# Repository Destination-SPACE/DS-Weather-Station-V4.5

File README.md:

<div align="center">
    
    <h1>Destination Weather Station v4.5.2</h1>
    <p>An Open Source Remote Sensing Platform for National Taiwan Normal University 🇹🇼</p>
</div>

## 🌟 About the Project
Destination Weather Station is the the latest version of remote sensing tools developed to teach students across Taiwan about climate science and remote sensing in partnership with National Taiwan Normal University.
## ⚙️ Hardware
All hardware files can be found [here](hardware/destinationWeatherStation_v4-5/)
## 💻 Software
All program files can be found [here](software)
## 🗂️ Documentation
Documentation for the weather station can be found [here](https://destination-space.gitlab.io/ds-weather-station-v4.5/)
## Licenses
Each of the above sections are individually licensed. Terms and conditions apply within their respective folders.

**Documentation - [Apache License 2.0](docs/LICENSE)** <br>
**Hardware - [CERN-OHL-P](hardware/destinationWeatherStation_v4-5//LICENSE)** <br>
**Software - [The MIT License](software/LICENSE)**

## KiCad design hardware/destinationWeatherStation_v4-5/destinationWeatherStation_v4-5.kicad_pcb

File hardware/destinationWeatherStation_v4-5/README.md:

# Destination Weather Station v4.5 Hardware
KiCad files for Destination Weather Station v4.5

## KiCanvas
View schematic and PCB files with [KiCanvas](https://kicanvas.org/?github=https%3A%2F%2Fgithub.com%2FDestination-SPACE%2FDS-Weather-Station-V4_5%2Ftree%2Fmain%2Fhardware%2FdestinationWeatherStation_v4-5)

## Directory
### [🧾 Bill of Materials](bom/bom.md)
### [📄 Datasheets](datasheets)
### [📐 Gerbers](gerber)
### [📰 Schematics](pdf)

Licensed under [CERN-OHL-P](LICENSE)

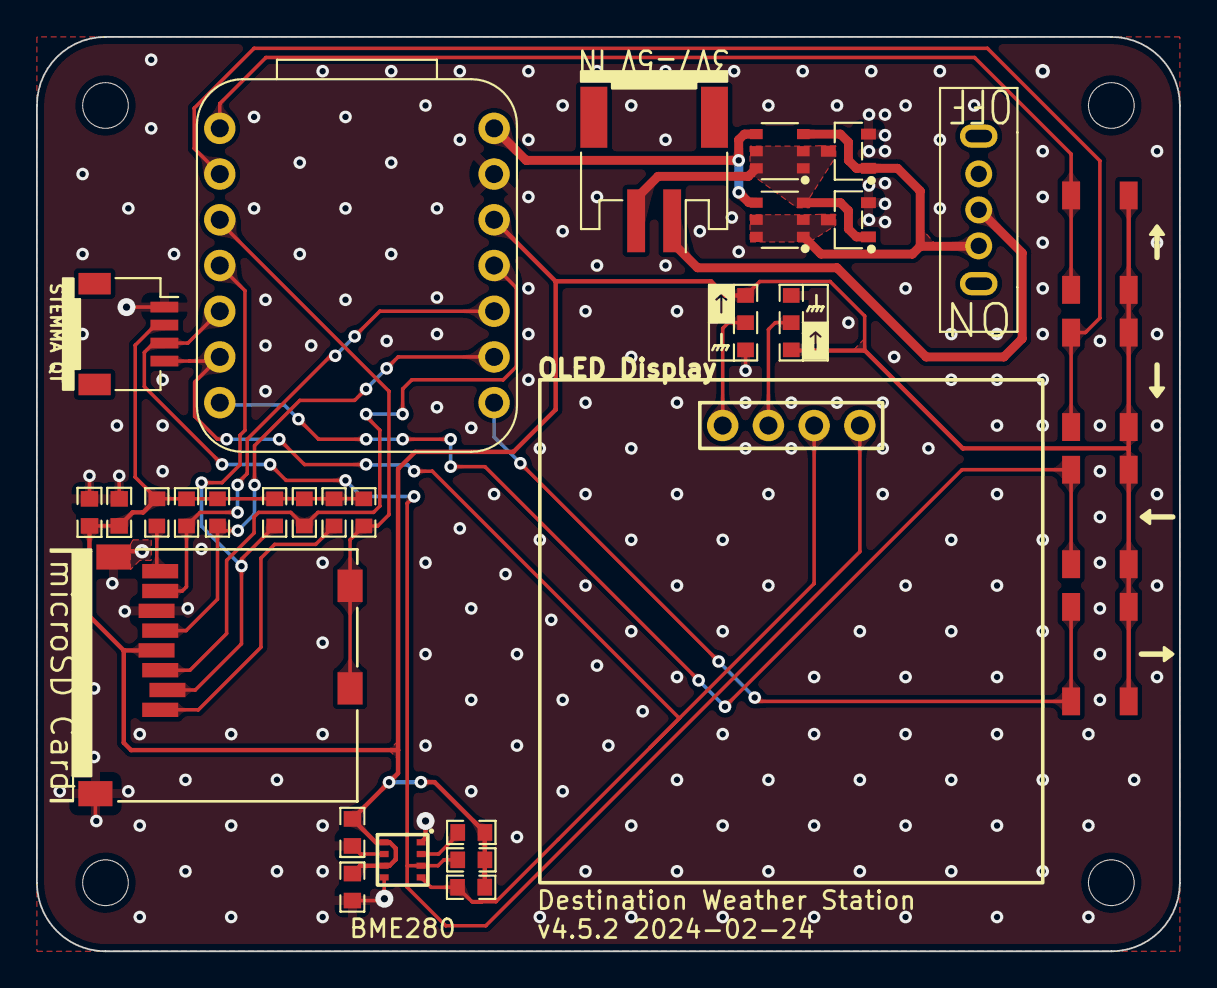
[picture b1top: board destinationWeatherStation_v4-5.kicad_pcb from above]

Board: 2 copper layers, 63.5 x 50.8 mm, 35 parts (0 on the bottom side), 22 nets.

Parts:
C1: 10uF; CAPC160X80X88L35N
C2, C3, C4: 100nF; CAPC160X80X88L35N
H1, H2, H3, H4: M2.5; M2.54_NPTH
J1: S2B-PH-SM4; JST-PH-S2B-SM4-TB
J2: MEM2061
J3: STEMMA_QT; JST_SH_SM04B-SRSS-TB
Q1, Q2: IRLML6244TRPBF
Q3, Q4: DMP2035UVTQ-7; SOT23-6P95_280X100L40X37N
R1, R2, R3, R4, R5, R6, R7, R8, R9, R10: 10K; RESC160X80X55L30N
R11, R12: 0R; ResistorJumper-3
SW1: SS-12F44-G5; SS-12D07-VG_GA_PA
SW2, SW3, SW4, SW5: PTS647SM38SMTR2LFS; SW_4.5x4.5
U1: XIAO RP2040; QtPy
U2: BME280
U3: HS96L03W2C03

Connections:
+3V3: C1.1, C2.1, C3.1, C4.1, J2.4 (VDD), J3.2, R1.1, R2.1, R3.1, R4.1, R5.1, R6.1, R7.1, R8.1, R9.1, R10.1, R11.1 (A), R12.3 (B), SW2.1, SW2.2, SW3.1, SW3.2, SW4.1, SW4.2, SW5.1, SW5.2, U1.12 (3V3), U2.6 (VDDIO), U2.8 (VDD)
/BME_CS: R8.2, U2.2 (CSB)
/CD: J2.9 (DET), R1.2, U1.3 (D2)
/CS_SD: J2.2 (DAT3/CD), R6.2, U1.4 (D3)
/DAT1: J2.8 (DAT1), R2.2
/DAT2: J2.1 (DAT2), R7.2
/MISO: J2.7 (DAT0), R3.2, U1.10 (D9)
/MOSI: J2.3 (CMD), R5.2, U1.11 (D10)
/OLED1: R11.2 (C), U3.1 (GND)
/OLED2: R12.2 (C), U3.2 (VCC)
/SCK: J2.5 (CLK), R4.2, U1.9 (D8)
/SCL: J3.4, R10.2, U1.6 (D5), U2.4 (SCK), U3.3 (SCL)
/SDA: J3.3, R9.2, U1.5 (D4), U2.3 (SDI), U3.4 (SDA)
/SW2: SW2.3, SW2.4, U1.1 (D0)
/SW3: SW3.3, SW3.4, U1.2 (D1)
/SW4: SW4.3, SW4.4, U1.7 (D6)
/SW5: SW5.3, SW5.4, U1.8 (D7)
GND: C1.2, C2.2, C3.2, C4.2, J2.6 (VSS), J2.10 (SHIELD), J3.1, Q1.2, Q2.2, R11.3 (B), R12.1 (A), U1.13 (GND), U2.1 (GND), U2.5 (SDO), U2.7 (GND)
unnamed: J1.1, SW1.2 (B)
unnamed: J1.2, Q1.1, Q2.3, Q3.3, Q4.1, Q4.2, Q4.5, Q4.6
unnamed: Q1.3, Q2.1, Q3.1, Q3.2, Q3.5, Q3.6, Q4.3, SW1.1 (A)
VCC: Q3.4, Q4.4, U1.14 (VIN)

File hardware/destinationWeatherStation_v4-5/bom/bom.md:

# Bill of Materials
*Note: Some parts may be replaced with suitable alternatives

| Item | Qty | Reference | Value | Datasheet | Manufacturer | Manufacturer Part Number | Package |
|-----:|----:|:---------:|:-----:|:----------|:-------------|:-------------------------|--------:|
| 1 | 1 | C1 | 10uF | [AVX-CX5R-KGM](../datasheets/AVX-CX5R-KGM-MLCC.pdf) | KYOCERA AVX | KGM15CR51A106MT | 0603 |
| 2 | 3 | C2, C3, C4 | 0.1uF | [AVX-CX5R-KGM](../datasheets/AVX-CX5R-KGM-MLCC.pdf) | KYOCERA AVX | KGM15AR51H104KT | 0603 | 
| 3 | 10 | R1, R2, R3, R4, R5, R6, R7, R8, R9, R10 | 10K | [D/CRCW e3](../datasheets/Vishay-Dale-DCRCWe3.pdf) | Vishay Dale | CRCW060310K0JNEB | 0603 |
| 3 | 2 | R11, R12 | 0R | [D/CRCW e3](../datasheets/Vishay-Dale-DCRCWe3.pdf) | Vishay Dale | CRCW06030000Z0EA | 0603 |
| 4 | 2 | Q1, Q2 | IRLML6244TRPBF | [IRLML6244TRPBF](../datasheets//Infineon-IRLML6244.pdf) | Infineon Technologies | IRLML6244TRPBF | SOT-23 |
| 5 | 2 | Q3, Q4 | DMP2035UVTQ | [DMP2035UVTQ](../datasheets/Diodes-Incorporated-DMP2035UVTQ.pdf) | Diodes Incorporated | DMP2035UVTQ-7 | TSOT26 |
| 6 | 1 | U1 | XIAO RP2040 | [XIAO RP2040](https://wiki.seeedstudio.com/XIAO-RP2040/) | Seeed Studio | XIAO RP2040 | N/A |
| 7 | 1 | U2 | BME280 | [BME280](../datasheets/BST-BME280.pdf) | Bosch Sensortec | BME280 | 2.5x2.5mm LGA |
| 8 | 1 | U3 | OLED | [HS96L03W2C03](../datasheets/HS-HS96L03W2C03.pdf) | SHENZHEN HANSHENG INDUSTRAIL CO. | HS96L03W2C03 | N/A |
| 9 | 1 | SW1 | SS-12F44-G5 | [SS-12F44-G5](../datasheets/SS-12D07-VG_GA_PA.pdf) | C&K | SS-12D07-VG 4 NS GA PA | N/A |
| 10 | 4 | SW2, SW3, SW4, SW5 | PTS647SM38SMTR2LFS | [PTS647SM38SMTR2LFS](../datasheets/C&K-PTS647.pdf) | C&K | PTS 647 SM38 SMTR2 LFS | N/A |
| 11 | 1 | J1 | S2B-PH-SM4 | [JST-PH](../datasheets/JST-PH-Connectors.pdf) | JST Sales America Inc. | S2B-PH-SM4-TB(LF)(SN) | N/A |
| 12 | 1 | J2 | MEM2061 | [MEM2061](../datasheets//GCT-MEM2061.pdf) | GCT | MEM2061-01-188-00-A | N/A |
| 13 | 1 | J3 | SM04B-SRSS | [JST-SH](../datasheets/JST-SH-Connectors.pdf) | JST Sales America Inc. | SM04B-SRSS-TB | N/A |

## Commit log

2023-12-26 test
2023-12-26 remove submodules
2024-01-14 add image
2024-01-14 created read.me
2024-01-15 edited docs README
2024-01-15 added READMEs for hardware and software
2024-01-15 added hardware files
2024-01-15 deleted ibom
2024-01-15 added BOM
2024-01-15 deleted old gerbers
2024-01-15 Hardware README
2024-01-15 fixed datasheets link
2024-01-15 added docs
2024-01-15 added dir to docs README
2024-01-15 Added HTML drop-down menus for directories
2024-01-15 Added to uploading-code.md
2024-01-15 removed &nbsp's
2024-01-15 fixed spacing
2024-01-15 fixed spacing again
2024-01-15 spacing
2024-01-15 revert spacing
2024-01-15 removed comments from style
2024-01-15 moved style
2024-01-15 reverting move of style
2024-01-16 added HTML tag for style
2024-01-16 moved HTML
2024-01-16 added style.css
2024-01-16 changed style to front matter
2024-01-16 front matter css tag
2024-01-16 changes css to inline with HTML
2024-01-16 changes margin
2024-01-16 changed margin
2024-01-16 removed css
2024-01-17 code changes
2024-01-30 exported blender files and added weather_station code file
2024-02-12 finalized PCB CAD
2024-02-13 added html files
2024-02-13 fixed stuff
2024-02-15 Add new file
2024-02-16 file touchups
2024-02-17 Add .gitlab-ci.yml
2024-02-17 html added
2024-02-17 fixed sphinx stuff
2024-02-17 Update .gitlab-ci.yml file
2024-02-17 edited yml
2024-02-17 moved doc files
2024-02-17 moved asset folder
2024-02-17 added docs link to README
2024-02-17 Add CERN-OHL-P LICENSE
2024-02-17 added images
2024-02-17 added licenses
2024-02-17 updated license agreements and diclosures
2024-02-17 kicad backups
2024-02-20 blender stuff
2024-02-20 full blender file and first render
2024-02-20 removed temp file
2024-02-24 3d pdf stuff and board fixes
2024-02-24 final CAD changes
2024-02-24 fixes
2024-02-26 cache
2024-02-28 assembly instructions
2024-03-03 gthyju
2024-03-04 fixed repaced wx stn code with demo, and modeified demo code
2024-03-04 trying to add PIO support for XIAORP2040
2024-03-04 test jig coad init
2024-03-04 test jig code
2024-03-05 backups
2024-03-06 sierra extension stuff
2024-03-07 blender renders
2024-03-08 blender changes
2024-03-08 updated ci/cl file
2024-03-08 cicl
2024-03-08 moved .gitlab-ci.yml to root
2024-03-08 updated ci/cl
2024-03-08 gdfg
2024-03-09 yml stuff
2024-03-09 asda
2024-03-09 change dir
2024-03-09 added rtd theme
2024-03-09 added assembly images
2024-03-09 fixed image refs
2024-03-09 list
2024-03-09 added iso
2024-03-09 install arduino ide changes
2024-03-10 sensor pages
2024-03-10 iso blend file
2024-03-10 added bme280 info
2024-03-10 fixed BME280 tables
2024-03-10 ens image
2024-03-11 deleted temp files. fixed .gitignore
2024-03-11 added wait for uSD connection
2024-03-11 ens160 info
2024-03-11 fixed link refs
2024-03-11 links
2024-03-11 fixed bme image
2024-03-11 fixed ens link
2024-03-11 deleted quotes on bme temp table
2024-03-11 added details about UV sensor
2024-03-11 added UV spectrum image
2024-03-11 added SCD40 info to docs
2024-03-11 fixed links?
2024-03-11 removed CNN test link
2024-03-11 added VEML7700 info
2024-03-11 fixed image ref
2024-03-11 save
2024-03-11 fixed resistor quantity
2024-03-12 added PDF build support
2024-03-12 fixed pdf build stuff?
2024-03-12 moved outputs
2024-03-12 moved output?
2024-03-12 added - make latexpdf
2024-03-12 fixed?
2024-03-12 try again
2024-03-12 new job
2024-03-12 add sphinx to other job
2024-03-13 removed calibration file
2024-03-13 removed tutorials
2024-03-13 reordered sensors
2024-03-13 removed WX STN config
2024-03-13 added hardware details
2024-03-13 removed i2c scanner page
2024-03-13 software pages
2024-03-13 fixed links
2024-03-13 fixed links again
2024-03-13 fixed links...
2024-03-14 pdf?
2024-03-14 add pdf export
2024-03-14 fixed dir
2024-03-14 fixed dir?
2024-03-14 added stuff
2024-03-14 fghj
2024-03-14 convert to make
2024-03-14 dssdg
2024-03-14 sdfgh
2024-03-14 dsafg
2024-03-14 dsgf
2024-03-14 pdf stuff
2024-03-14 gitignore
2024-03-14 moved gitignore
2024-03-14 hfgh
2024-03-14 updated gitignore
2024-03-19 changed file names
2024-03-19 balloon mount assembly and stl
2024-03-19 slice
2024-03-19 updated links
2024-03-21 created sensor activity pages
2024-03-21 reduced tree depth
2024-03-21 caption
2024-03-21 added captions
2024-03-21 added misc caption
2024-03-21 fixed headers
2024-03-21 fixed header
2024-03-26 added details to blink function
2024-03-26 words
2024-03-26 fixed formatting
2024-03-26 reordered library section
2024-03-26 sensor test program overview
2024-03-26 added .vscode
2024-03-26 edited modification date
2024-03-28 added activities
2024-03-28 Added activity sections
2024-03-28 spelling
2024-03-28 converted list to toctree
2024-03-28 toctree formatting
2024-03-28 titles
2024-03-28 named activity
2024-03-28 experiments
2024-03-28 new KiCanvas link
2024-03-29 brief descriptions
2024-04-02 added button menu instructions
2024-04-02 fixed code to work with or without expansion sensors
2024-04-02 changed weather station version number
2024-04-02 Added details
2024-04-02 fixed heat-index formula
2024-04-02 wrap-text HI equation
2024-04-02 nowrap
2024-04-02 TVOC updates
2024-04-02 finished
2024-04-02 fixed AQI code
2024-04-02 fixed code-block spacing
2024-04-04 weather station overview picture
2024-04-05 adding debug stuff
2024-04-06 added card detect functionality
2024-04-06 demo fixes
